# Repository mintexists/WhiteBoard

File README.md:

# WhiteBoard

## A Budget-Oriented Ortholinear Keyboard

Current Version 1.1 - Adds support for pcb mount stabilizers, makes the design easier to assemble, and decreases price of production

Planned Improvements - Add support for an acrylic window for the components on the left

## Features
- Rotary Encoder
- Hot Swappable switches
- QMK and VIA support (Not upstream)
- Easy Assembly (Can be made entirely through hole)
- Budget Oriented
- Compatible with a variety of Microcontrollers

## Make Your Own

[Parts List](PartsList.md)

A Build Guide will be added shortly

## Images

## My Keymap

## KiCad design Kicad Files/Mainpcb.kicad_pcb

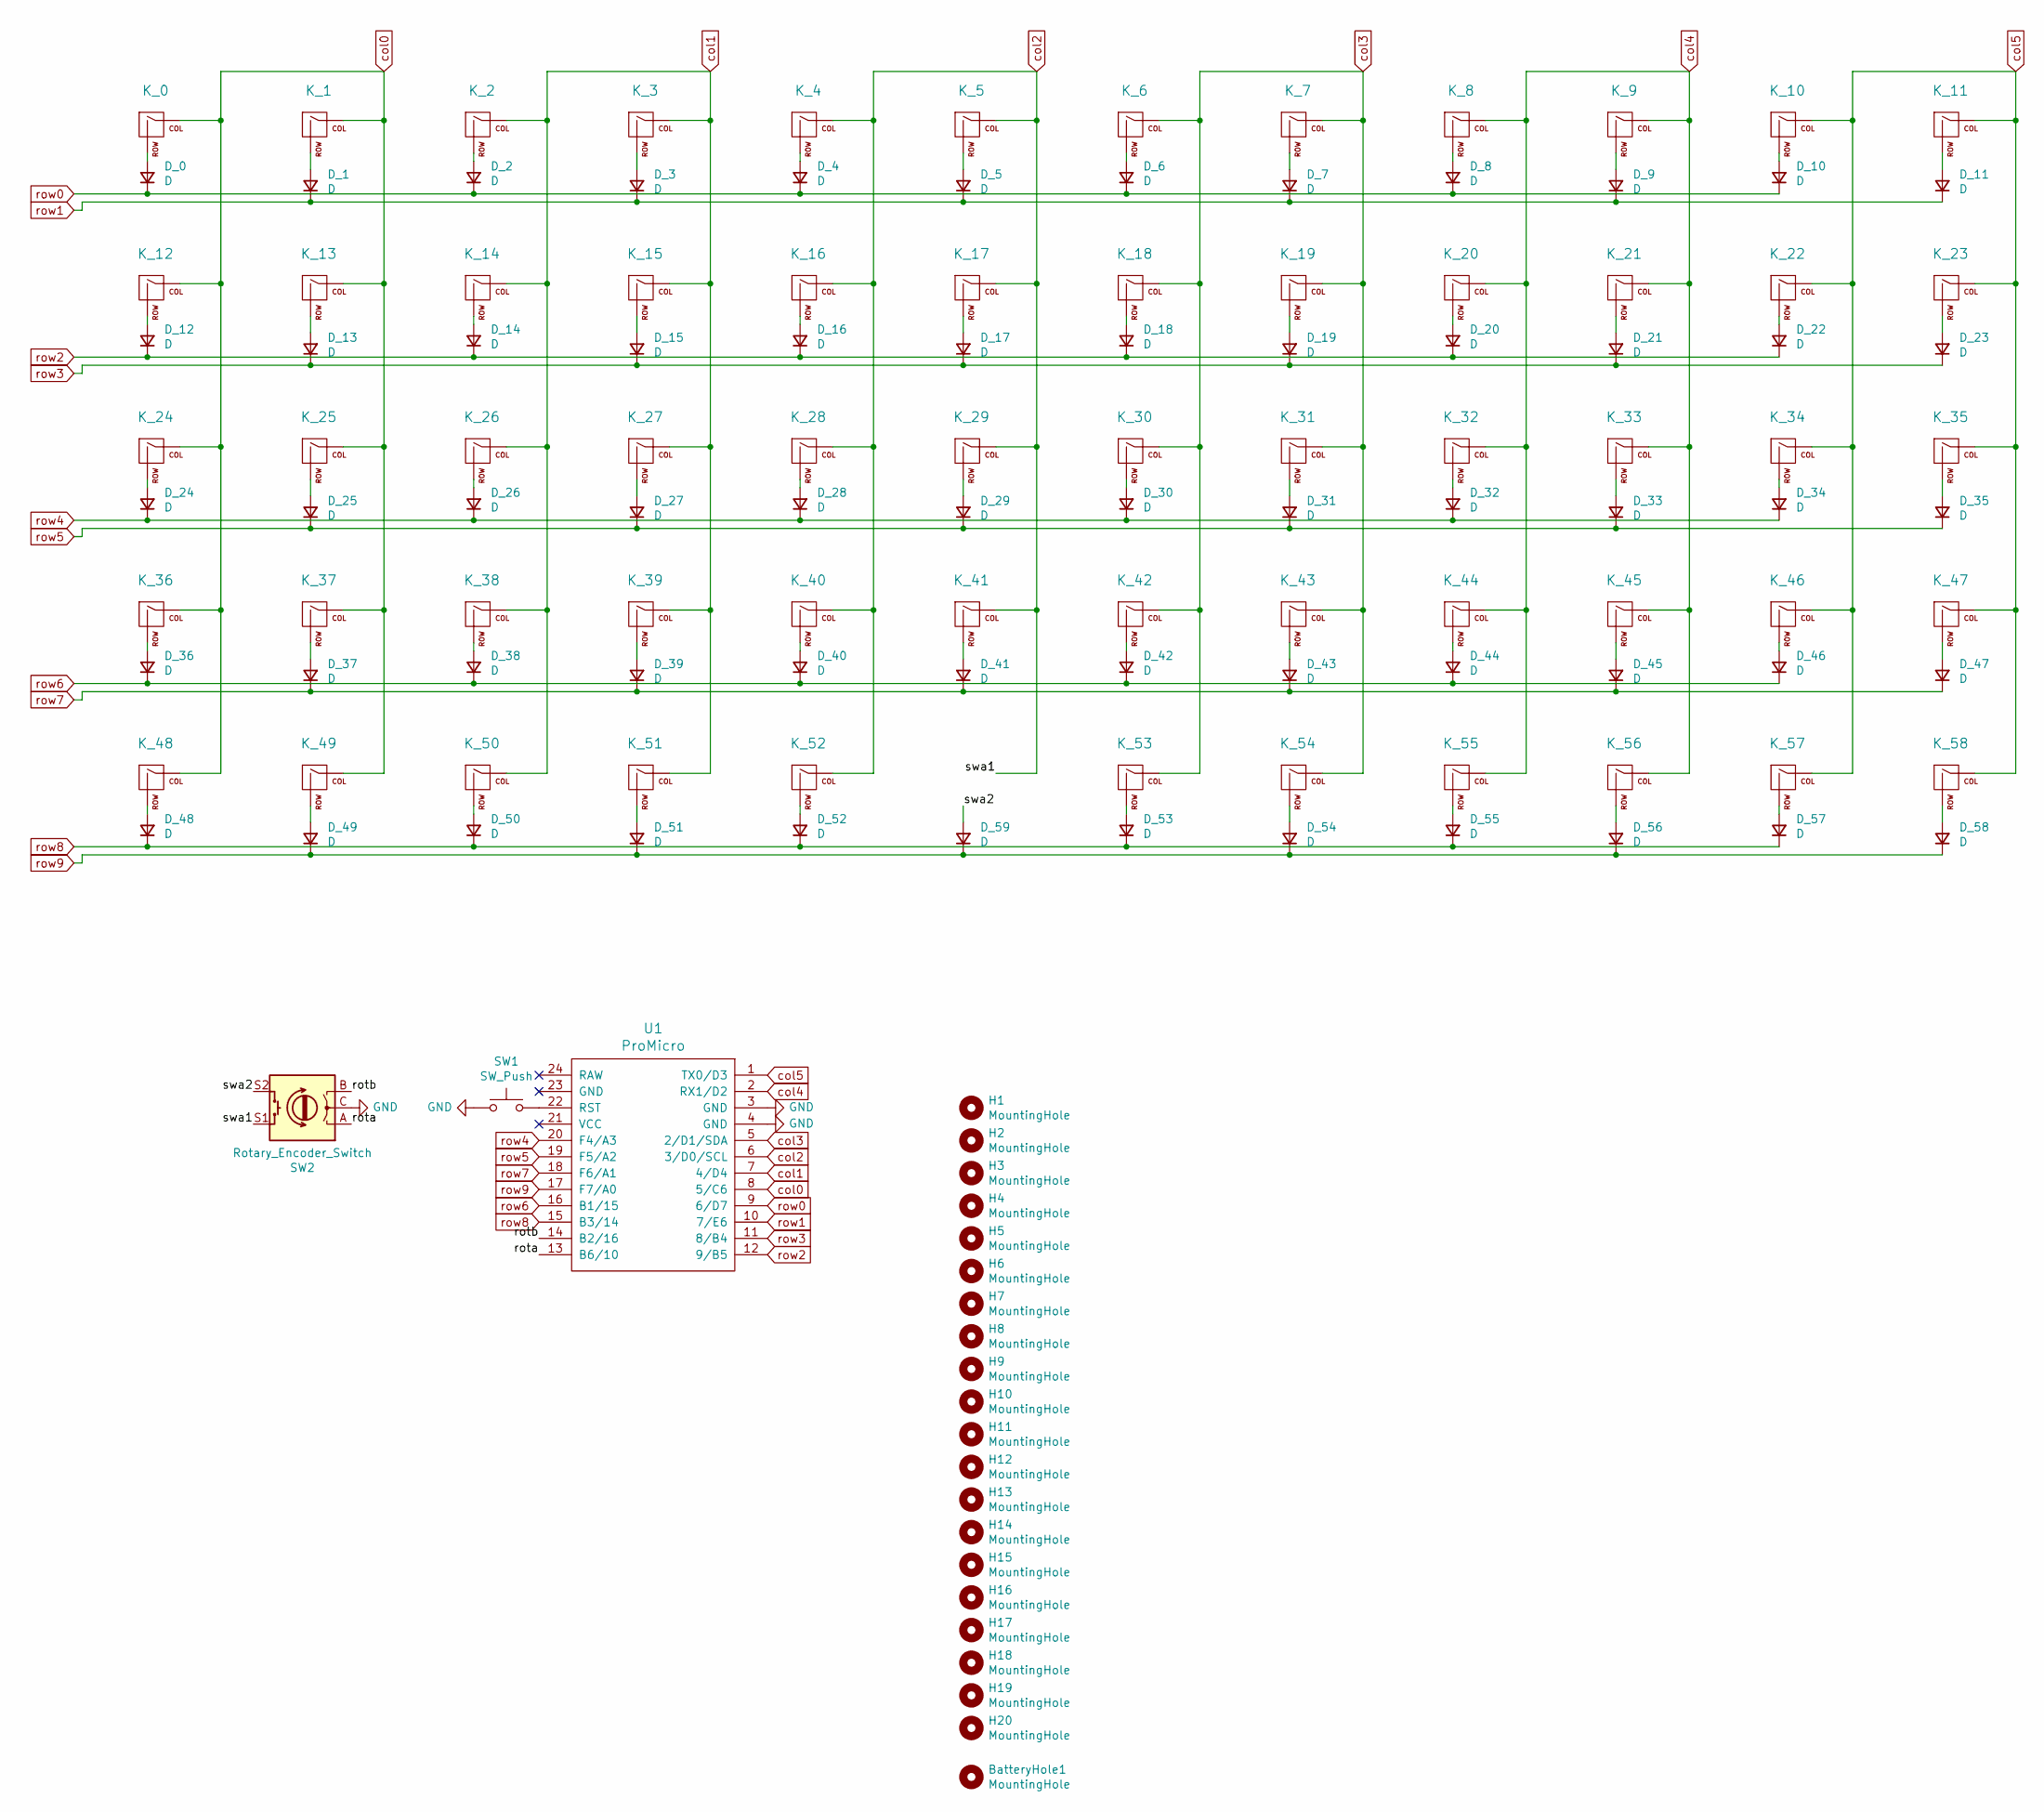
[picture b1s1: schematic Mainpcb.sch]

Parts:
BatteryHole1: MountingHole; MountingHole_5.3mm_M5
D_0, D_1, D_2, D_3, D_4, D_5, D_6, D_7, D_8, D_9, D_10, D_11, D_12, D_13, D_14, D_15, D_16, D_17, D_18, D_19, D_20, D_21, D_22, D_23, D_24, D_25, D_26, D_27, D_28, D_29, D_30, D_31, D_32, D_33, D_34, D_35, D_36, D_37, D_38, D_39, D_40, D_41, D_42, D_43, D_44, D_45, D_46, D_47, D_48, D_49, D_50, D_51, D_52, D_53, D_54, D_55, D_56, D_57, D_58, D_59: D; D_SOD123_axial
H1, H2, H3, H4, H5, H6, H7, H8, H9, H10: MountingHole; MountingHole_2.2mm_M2
H11, H12, H13, H14, H15, H16, H17, H18, H19, H20: MountingHole; MountingHole_3.5mm
K_0, K_1, K_2, K_3, K_4, K_5, K_6, K_7, K_8, K_9, K_10, K_11, K_12, K_13, K_14, K_15, K_16, K_17, K_18, K_19, K_20, K_21, K_22, K_23, K_24, K_25, K_26, K_27, K_28, K_29, K_30, K_31, K_32, K_33, K_34, K_35, K_36, K_37, K_38, K_39, K_40, K_41, K_42, K_43, K_44, K_45, K_46, K_47, K_48, K_49, K_50, K_51, K_52, K_53, K_54, K_55, K_56, K_57, K_58: KEYSW; Kailh_socket_MX
SW1: SW_Push; SW_Push_1P1T_NO_6x6mm_H9.5mm
SW2: Rotary_Encoder_Switch; RotaryEncoder_Alps_EC11E-Switch_Vertical_H20mm
U1: ProMicro; ArduinoProMicro-ZigZag

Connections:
/rota: SW2.A, U1.13 (B6/10)
/rotb: SW2.B, U1.14 (B2/16)
/swa2: D_59.2 (A), SW2.S2
GND: SW1.2, SW2.C, U1.3 (GND), U1.4 (GND)
unnamed: D_0.2 (A), K_0.2 (ROW)
unnamed: D_1.2 (A), K_1.2 (ROW)
unnamed: D_2.2 (A), K_2.2 (ROW)
unnamed: D_3.2 (A), K_3.2 (ROW)
unnamed: D_4.2 (A), K_4.2 (ROW)
unnamed: D_5.2 (A), K_5.2 (ROW)
unnamed: D_6.2 (A), K_6.2 (ROW)
unnamed: D_7.2 (A), K_7.2 (ROW)
unnamed: D_8.2 (A), K_8.2 (ROW)
unnamed: D_9.2 (A), K_9.2 (ROW)
unnamed: D_10.2 (A), K_10.2 (ROW)
unnamed: D_11.2 (A), K_11.2 (ROW)
unnamed: D_12.2 (A), K_12.2 (ROW)
unnamed: D_13.2 (A), K_13.2 (ROW)
unnamed: D_14.2 (A), K_14.2 (ROW)
unnamed: D_15.2 (A), K_15.2 (ROW)
unnamed: D_16.2 (A), K_16.2 (ROW)
unnamed: D_17.2 (A), K_17.2 (ROW)
unnamed: D_18.2 (A), K_18.2 (ROW)
unnamed: D_19.2 (A), K_19.2 (ROW)
unnamed: D_20.2 (A), K_20.2 (ROW)
unnamed: D_21.2 (A), K_21.2 (ROW)
unnamed: D_22.2 (A), K_22.2 (ROW)
unnamed: D_23.2 (A), K_23.2 (ROW)
unnamed: D_24.2 (A), K_24.2 (ROW)
unnamed: D_25.2 (A), K_25.2 (ROW)
unnamed: D_26.2 (A), K_26.2 (ROW)
unnamed: D_27.2 (A), K_27.2 (ROW)
unnamed: D_28.2 (A), K_28.2 (ROW)
unnamed: D_29.2 (A), K_29.2 (ROW)
unnamed: D_30.2 (A), K_30.2 (ROW)
unnamed: D_31.2 (A), K_31.2 (ROW)
unnamed: D_32.2 (A), K_32.2 (ROW)
unnamed: D_33.2 (A), K_33.2 (ROW)
unnamed: D_34.2 (A), K_34.2 (ROW)
unnamed: D_35.2 (A), K_35.2 (ROW)
unnamed: D_36.2 (A), K_36.2 (ROW)
unnamed: D_37.2 (A), K_37.2 (ROW)
unnamed: D_38.2 (A), K_38.2 (ROW)
unnamed: D_39.2 (A), K_39.2 (ROW)
unnamed: D_40.2 (A), K_40.2 (ROW)
unnamed: D_41.2 (A), K_41.2 (ROW)
unnamed: D_42.2 (A), K_42.2 (ROW)
unnamed: D_43.2 (A), K_43.2 (ROW)
unnamed: D_44.2 (A), K_44.2 (ROW)
unnamed: D_45.2 (A), K_45.2 (ROW)
unnamed: D_46.2 (A), K_46.2 (ROW)
unnamed: D_47.2 (A), K_47.2 (ROW)
unnamed: D_48.2 (A), K_48.2 (ROW)
unnamed: D_49.2 (A), K_49.2 (ROW)
unnamed: D_50.2 (A), K_50.2 (ROW)
unnamed: D_51.2 (A), K_51.2 (ROW)
unnamed: D_52.2 (A), K_52.2 (ROW)
unnamed: D_53.2 (A), K_53.2 (ROW)
unnamed: D_54.2 (A), K_54.2 (ROW)
unnamed: D_55.2 (A), K_55.2 (ROW)
unnamed: D_56.2 (A), K_56.2 (ROW)
unnamed: D_57.2 (A), K_57.2 (ROW)
unnamed: D_58.2 (A), K_58.2 (ROW)
unnamed: SW1.1, U1.22 (RST)
col0: K_0.1 (COL), K_1.1 (COL), K_12.1 (COL), K_13.1 (COL), K_24.1 (COL), K_25.1 (COL), K_36.1 (COL), K_37.1 (COL), K_48.1 (COL), K_49.1 (COL), U1.8 (5/C6)
col1: K_2.1 (COL), K_3.1 (COL), K_14.1 (COL), K_15.1 (COL), K_26.1 (COL), K_27.1 (COL), K_38.1 (COL), K_39.1 (COL), K_50.1 (COL), K_51.1 (COL), U1.7 (4/D4)
col2: K_4.1 (COL), K_5.1 (COL), K_16.1 (COL), K_17.1 (COL), K_28.1 (COL), K_29.1 (COL), K_40.1 (COL), K_41.1 (COL), K_52.1 (COL), SW2.S1, U1.6 (3/D0/SCL)
col3: K_6.1 (COL), K_7.1 (COL), K_18.1 (COL), K_19.1 (COL), K_30.1 (COL), K_31.1 (COL), K_42.1 (COL), K_43.1 (COL), K_53.1 (COL), K_54.1 (COL), U1.5 (2/D1/SDA)
col4: K_8.1 (COL), K_9.1 (COL), K_20.1 (COL), K_21.1 (COL), K_32.1 (COL), K_33.1 (COL), K_44.1 (COL), K_45.1 (COL), K_55.1 (COL), K_56.1 (COL), U1.2 (RX1/D2)
col5: K_10.1 (COL), K_11.1 (COL), K_22.1 (COL), K_23.1 (COL), K_34.1 (COL), K_35.1 (COL), K_46.1 (COL), K_47.1 (COL), K_57.1 (COL), K_58.1 (COL), U1.1 (TX0/D3)
row0: D_0.1 (K), D_2.1 (K), D_4.1 (K), D_6.1 (K), D_8.1 (K), D_10.1 (K), U1.9 (6/D7)
row1: D_1.1 (K), D_3.1 (K), D_5.1 (K), D_7.1 (K), D_9.1 (K), D_11.1 (K), U1.10 (7/E6)
row2: D_12.1 (K), D_14.1 (K), D_16.1 (K), D_18.1 (K), D_20.1 (K), D_22.1 (K), U1.12 (9/B5)
row3: D_13.1 (K), D_15.1 (K), D_17.1 (K), D_19.1 (K), D_21.1 (K), D_23.1 (K), U1.11 (8/B4)
row4: D_24.1 (K), D_26.1 (K), D_28.1 (K), D_30.1 (K), D_32.1 (K), D_34.1 (K), U1.20 (F4/A3)
row5: D_25.1 (K), D_27.1 (K), D_29.1 (K), D_31.1 (K), D_33.1 (K), D_35.1 (K), U1.19 (F5/A2)
row6: D_36.1 (K), D_38.1 (K), D_40.1 (K), D_42.1 (K), D_44.1 (K), D_46.1 (K), U1.16 (B1/15)
row7: D_37.1 (K), D_39.1 (K), D_41.1 (K), D_43.1 (K), D_45.1 (K), D_47.1 (K), U1.18 (F6/A1)
row8: D_48.1 (K), D_50.1 (K), D_52.1 (K), D_53.1 (K), D_55.1 (K), D_57.1 (K), U1.15 (B3/14)
row9: D_49.1 (K), D_51.1 (K), D_54.1 (K), D_56.1 (K), D_58.1 (K), D_59.1 (K), U1.17 (F7/A0)

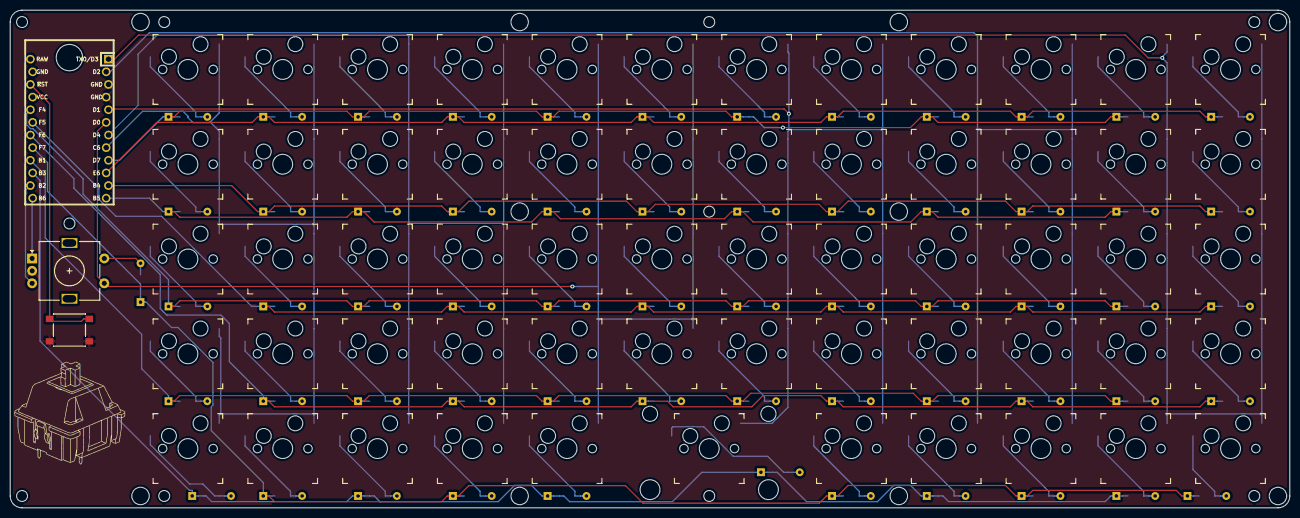
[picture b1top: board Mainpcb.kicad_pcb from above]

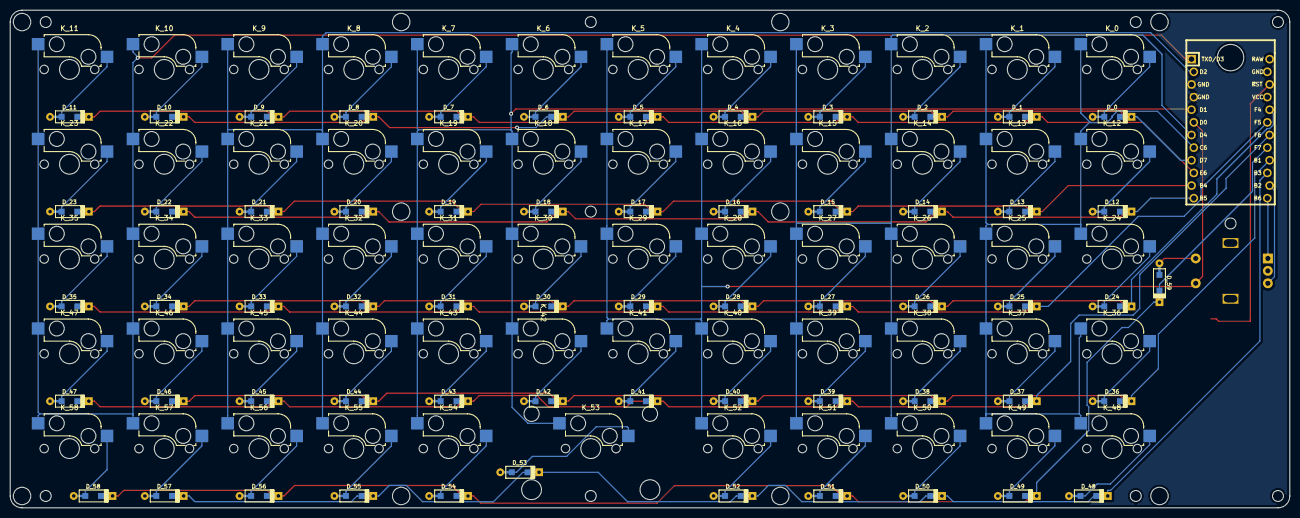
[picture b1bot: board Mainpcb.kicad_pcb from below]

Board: 2 copper layers, 257.2 x 100.0 mm, 143 parts (61 on the bottom side), 80 nets.

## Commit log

2021-06-15 Create a
2021-06-15 keymap images
2021-06-17 Upload kicad files
2021-06-18 Fix the kicad library locations
2021-06-18 Fixed files and imroved pcb design
2021-06-18 Small change
2021-06-18 Add Firmware
2021-06-18 Add Gerbers
